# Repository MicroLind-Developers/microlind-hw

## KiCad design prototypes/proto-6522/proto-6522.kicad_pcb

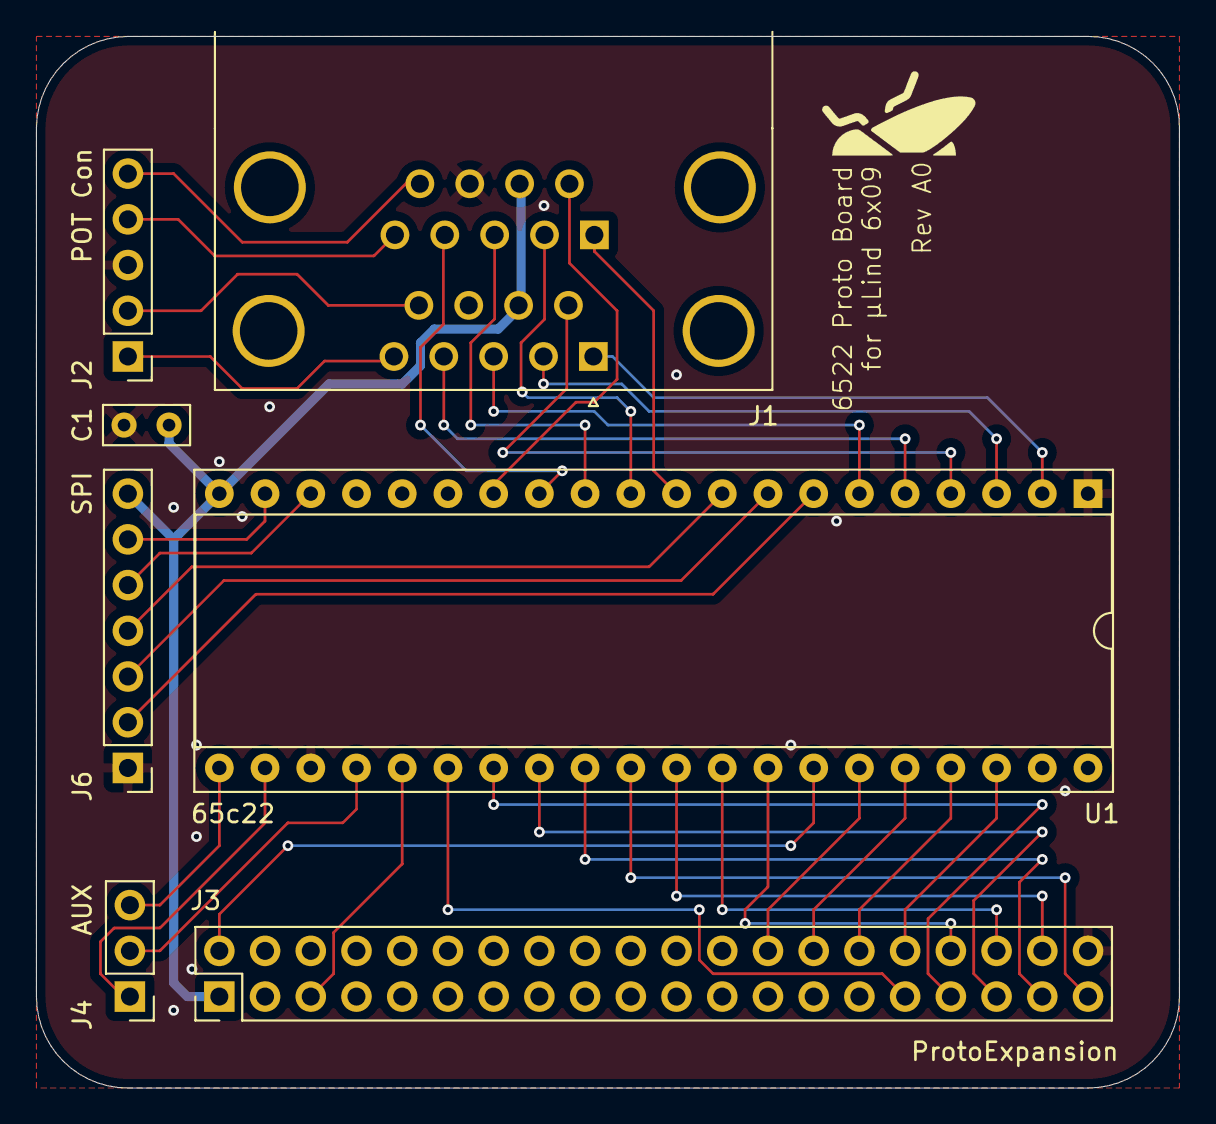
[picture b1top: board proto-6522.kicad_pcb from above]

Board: 2 copper layers, 63.5 x 58.4 mm, 7 parts (0 on the bottom side), 38 nets.

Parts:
C1: C; C_Rect_L4.6mm_W2.0mm_P2.50mm_MKS02_FKP02
J1: DSUB-9-Double_NorComp
J2: POT Con; PinHeader_1x05_P2.54mm_Vertical
J3: ProtoExpansion; PinHeader_2x20_P2.54mm_Vertical
J4: AUX; PinHeader_1x03_P2.54mm_Vertical
J6: SPI; PinHeader_1x07_P2.54mm_Vertical
U1: 65c22; DIP-40_W15.24mm_Socket

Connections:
/A0: J3.32, U1.38 (RS0)
/A1: J3.30, U1.37 (RS1)
/A2: J3.28, U1.36 (RS2)
/A3: J3.26, U1.35 (RS3)
/COPI/CIPO: J6.6, U1.19 (CB2)
/CS0: J6.2, U1.7 (PA5)
/CS1: J6.3, U1.8 (PA6)
/CS2: J6.4, U1.9 (PA7)
/D0: J3.34, U1.33 (D0)
/D1: J3.36, U1.32 (D1)
/D2: J3.38, U1.31 (D2)
/D3: J3.39, U1.30 (D3)
/D4: J3.37, U1.29 (D4)
/D5: J3.35, U1.28 (D5)
/D6: J3.33, U1.27 (D6)
/D7: J3.31, U1.26 (D7)
/E: J3.5, U1.25 (ϕ2)
/R/~W: J4.1, U1.22 (R/~W)
/SCK: J6.5, U1.18 (CB1)
/~INT_PAR: J4.3, U1.21 (~IRQ)
/~PAR_EN: J4.2, U1.24 (CS1)
/~RST: J3.2, U1.34 (~RES)
GND: C1.2, J1.8, J1.18, J2.3, J3.40, J6.1, U1.1 (VSS), U1.23 (~CS2)
unnamed: J1.5, J2.1
unnamed: J1.9, J2.2
unnamed: J1.15, J2.4
unnamed: J1.19, J2.5
unnamed: J1.1, U1.2 (PA0)
unnamed: J1.2, U1.3 (PA1)
unnamed: J1.6, U1.4 (PA2)
unnamed: J1.4, U1.5 (PA3)
unnamed: J1.3, U1.6 (PA4)
unnamed: J1.11, U1.10 (PB0)
unnamed: J1.12, U1.11 (PB1)
unnamed: J1.13, U1.12 (PB2)
unnamed: J1.14, U1.13 (PB3)
unnamed: J1.16, U1.14 (PB4)
VCC: C1.1, J1.7, J1.17, J3.1, J6.7, U1.20 (VCC)

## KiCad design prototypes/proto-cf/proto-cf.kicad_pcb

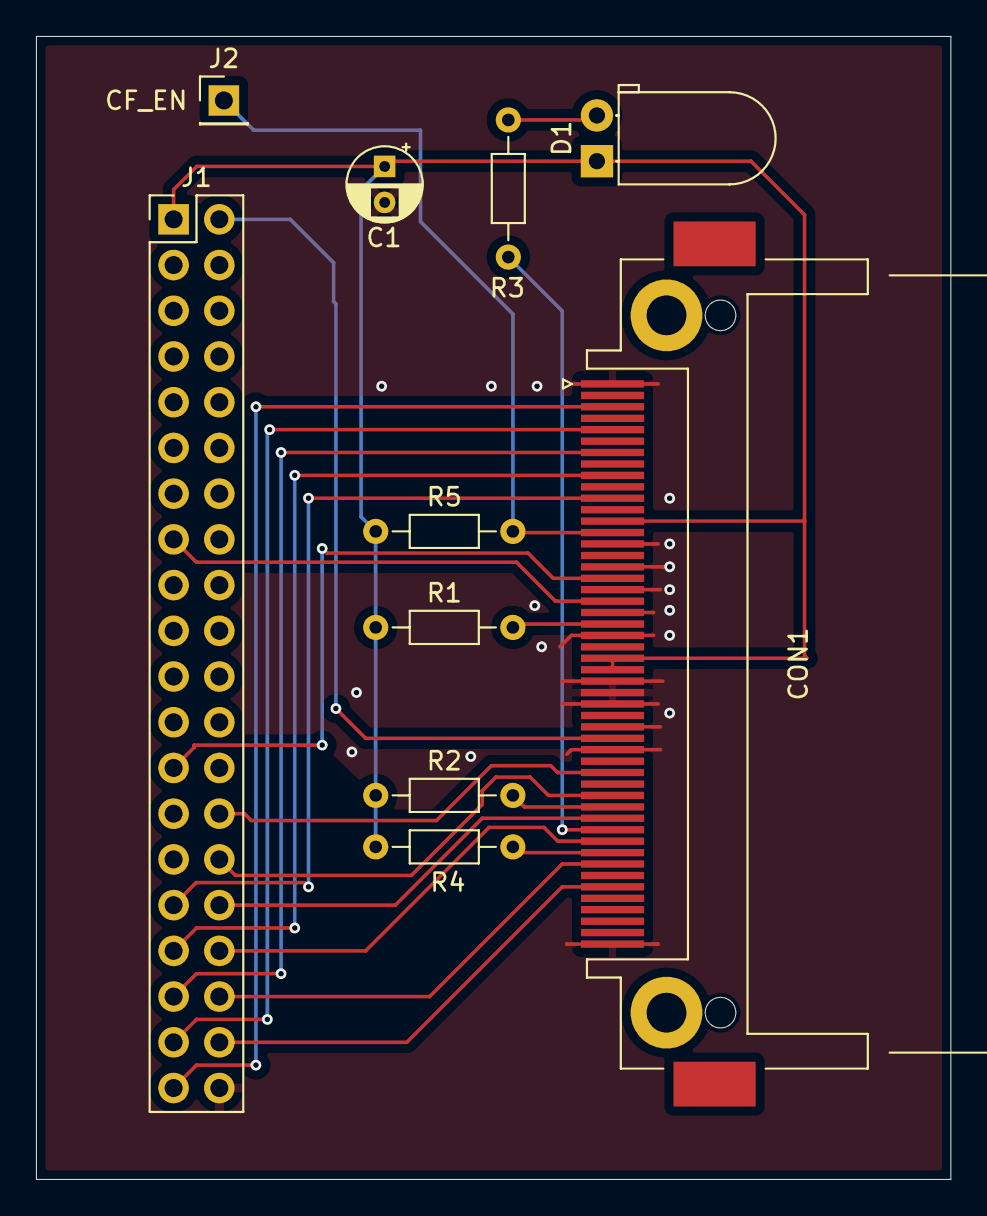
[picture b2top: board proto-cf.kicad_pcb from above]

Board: 2 copper layers, 50.8 x 63.5 mm, 10 parts (0 on the bottom side), 22 nets.

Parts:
C1: C_Polarized; CP_Radial_D4.0mm_P2.00mm
CON1: CF-CARD; CF-Card_3M_N7E50-7516PK-20-WF
D1: LED; LED_D5.0mm_Horizontal_O1.27mm_Z3.0mm_Clear
J1: VideoExpansion; PinHeader_2x20_P2.54mm_Vertical
J2: CF_EN; PinHeader_1x01_P2.54mm_Vertical
R1, R2, R3, R4, R5: 4k7; R_Axial_DIN0204_L3.6mm_D1.6mm_P7.62mm_Horizontal

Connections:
/A0: CON1.20 (A0), J1.32
/A1: CON1.19 (A1), J1.30
/A2: CON1.18 (A2), J1.28
/D0: CON1.21 (D0), J1.34
/D1: CON1.22 (D1), J1.36
/D2: CON1.23 (D2), J1.38
/D3: CON1.2 (D3), J1.39
/D4: CON1.3 (D4), J1.37
/D5: CON1.4 (D5), J1.35
/D6: CON1.5 (D6), J1.33
/D7: CON1.6 (D7), J1.31
/~CF_EN: CON1.32 (/CS1), J2.1, R5.2
/~RD: CON1.34 (/IORD), J1.25
/~RST: CON1.41 (/RESET), J1.2
/~WR: CON1.35 (/IOWR), J1.15
GND: C1.2, CON1.1 (GND1), CON1.8 (A10), CON1.9 (/ATASEL), CON1.10 (A9), CON1.11 (A8), CON1.12 (A7), CON1.14 (A6), CON1.15 (A5), CON1.16 (A4), CON1.17 (A3), CON1.39 (/CSEL), CON1.50 (GND2), J1.40
unnamed: CON1.45 (/DASP), R3.2
unnamed: CON1.46 (/PDIAG), R4.2
unnamed: CON1.44 (/REG), R2.2
unnamed: CON1.36 (/WE), R1.2
unnamed: D1.2 (A), R3.1
VCC: C1.1, CON1.7 (/CS0), CON1.13 (VCC2), CON1.38 (VCC1), D1.1 (K), J1.1, R1.1, R2.1, R4.1, R5.1

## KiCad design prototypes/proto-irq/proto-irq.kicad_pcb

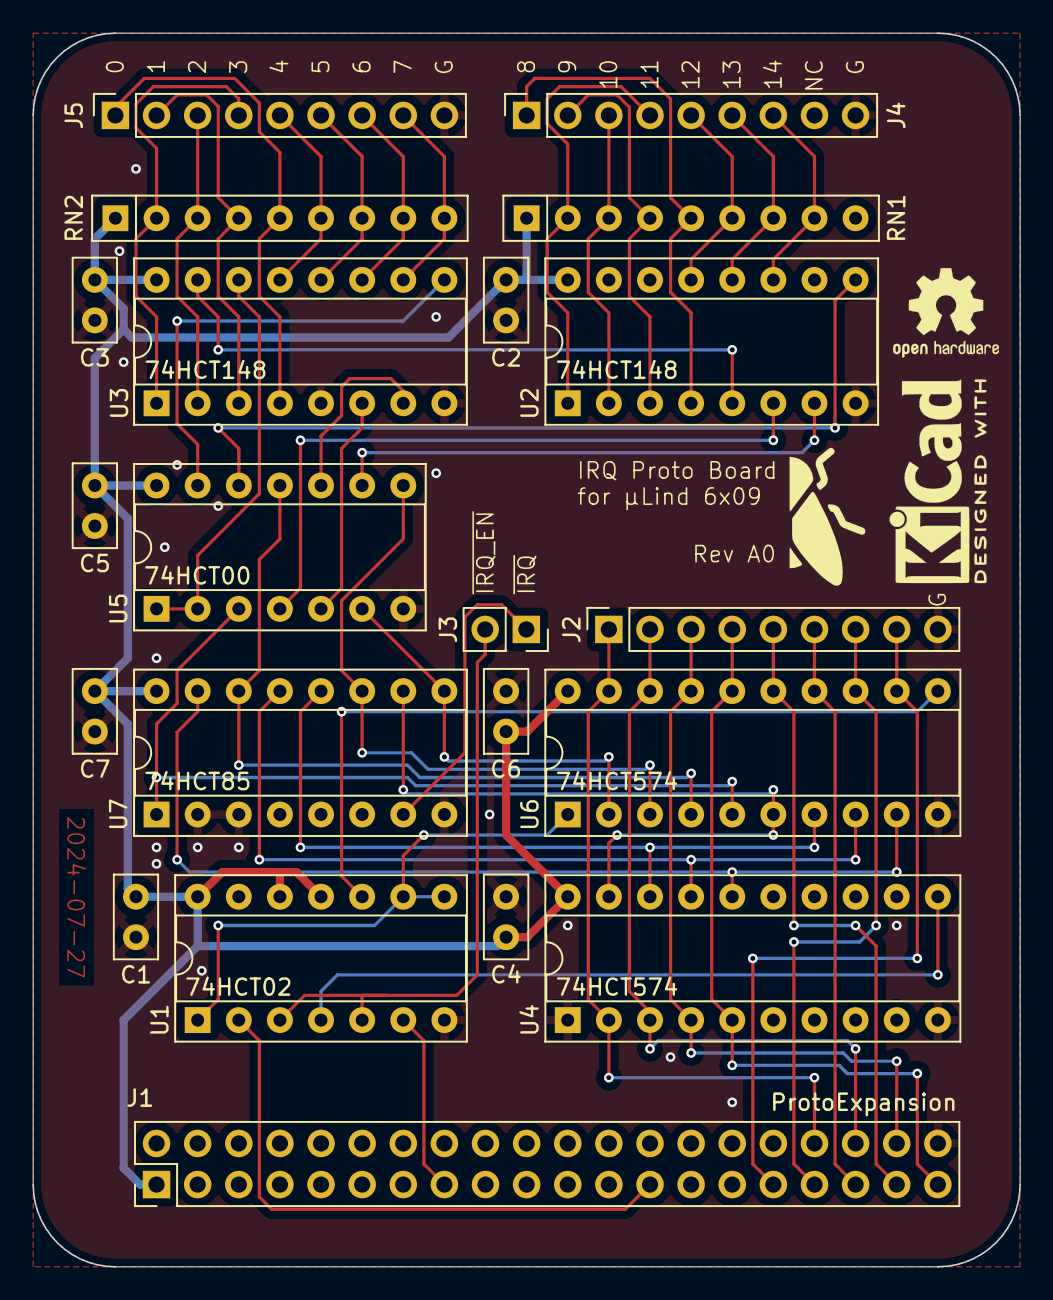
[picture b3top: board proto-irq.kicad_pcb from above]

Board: 2 copper layers, 61.0 x 76.2 mm, 21 parts (0 on the bottom side), 48 nets.

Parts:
C1, C2, C3, C4, C5, C6, C7: 100n; C_Disc_D5.0mm_W2.5mm_P2.50mm
J1: ProtoExpansion; PinHeader_2x20_P2.54mm_Vertical
J2: DataValue; PinSocket_1x09_P2.54mm_Vertical
J3: AUX; PinSocket_1x02_P2.54mm_Vertical
J4: Low IRQ; PinSocket_1x09_P2.54mm_Vertical
J5: High IRQ; PinSocket_1x09_P2.54mm_Vertical
RN1, RN2: R_Network08; R_Array_SIP9
U1: 74HCT02; DIP-14_W7.62mm_Socket
U2, U3: 74HCT148; DIP-16_W7.62mm_Socket
U4, U6: 74HCT574; DIP-20_W7.62mm_Socket
U5: 74HCT00; DIP-14_W7.62mm_Socket
U7: 74HCT85; DIP-16_W7.62mm_Socket

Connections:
/D0: J1.34, J2.1, U4.2 (D0), U6.19 (Q0)
/D1: J1.36, J2.2, U4.3 (D1), U6.18 (Q1)
/D2: J1.38, J2.3, U4.4 (D2), U6.17 (Q2)
/D3: J1.39, J2.4, U4.5 (D3), U6.16 (Q3)
/D4: J1.37, J2.5, U6.15 (Q4)
/D5: J1.35, J2.6, U6.14 (Q5)
/D6: J1.33, J2.7, U6.13 (Q6)
/D7: J1.31, J2.8, U6.12 (Q7)
/~IRQ_EN: J3.2, U1.3, U1.5
/~IRQ: J3.1, U7.7 (Oa<b)
/~RD: J1.25, U1.2
/~WR: J1.15, U1.6
GND: C1.2, C2.2, C3.2, C4.2, C5.2, C6.2, C7.2, J1.40, J2.9, J4.9, J5.9, U1.7 (GND), U2.8 (GND), U3.5 (EI), U3.8 (GND), U4.1 (OE), U4.10 (GND), U5.7 (GND), U6.10 (GND), U7.2 (Ia<b), U7.3 (Ia=b), U7.4 (Ia>b), U7.8 (GND)
unnamed: U2.5 (EI), U3.15 (EO)
unnamed: U2.9 (S0), U5.12
unnamed: U2.7 (S1), U5.9
unnamed: U2.6 (S2), U5.4
unnamed: U3.14 (GS), U5.1, U5.2
unnamed: U3.9 (S0), U5.13
unnamed: U3.7 (S1), U5.10
unnamed: U3.6 (S2), U5.5
unnamed: U1.4, U4.11 (Cp)
unnamed: U4.19 (Q0), U6.6 (D4), U7.10 (A0)
unnamed: U4.18 (Q1), U6.7 (D5), U7.12 (A1)
unnamed: U4.17 (Q2), U6.8 (D6), U7.13 (A2)
unnamed: U4.16 (Q3), U6.9 (D7), U7.15 (A3)
unnamed: U1.10, U6.11 (Cp)
unnamed: U5.6, U6.2 (D0), U7.9 (B0)
unnamed: U5.8, U6.3 (D1), U7.11 (B1)
unnamed: U5.11, U6.4 (D2), U7.14 (B2)
unnamed: U5.3, U6.5 (D3), U7.1 (B3)
unnamed: U1.1, U1.8, U1.9, U6.1 (OE)
VCC: C1.1, C2.1, C3.1, C4.1, C5.1, C6.1, C7.1, J1.1, RN1.1 (common), RN2.1 (common), U1.11, U1.12, U1.14 (VCC), U2.16 (VCC), U3.16 (VCC), U4.20 (VCC), U5.14 (VCC), U6.20 (VCC), U7.16 (VCC)
~IRQ_0: J5.1, RN2.5 (R4), U3.4 (I7)
~IRQ_1: J5.2, RN2.4 (R3), U3.3 (I6)
~IRQ_2: J5.3, RN2.3 (R2), U3.2 (I5)
~IRQ_3: J5.4, RN2.2 (R1), U3.1 (I4)
~IRQ_4: J5.5, RN2.6 (R5), U3.13 (I3)
~IRQ_5: J5.6, RN2.7 (R6), U3.12 (I2)
~IRQ_6: J5.7, RN2.8 (R7), U3.11 (I1)
~IRQ_7: J5.8, RN2.9 (R8), U3.10 (IO)
~IRQ_8: J4.1, RN1.5 (R4), U2.4 (I7)
~IRQ_9: J4.2, RN1.4 (R3), U2.3 (I6)
~IRQ_10: J4.3, RN1.3 (R2), U2.2 (I5)
~IRQ_11: J4.4, RN1.2 (R1), U2.1 (I4)
~IRQ_12: J4.5, RN1.6 (R5), U2.13 (I3)
~IRQ_13: J4.6, RN1.7 (R6), U2.12 (I2)
~IRQ_14: J4.7, RN1.8 (R7), U2.11 (I1)

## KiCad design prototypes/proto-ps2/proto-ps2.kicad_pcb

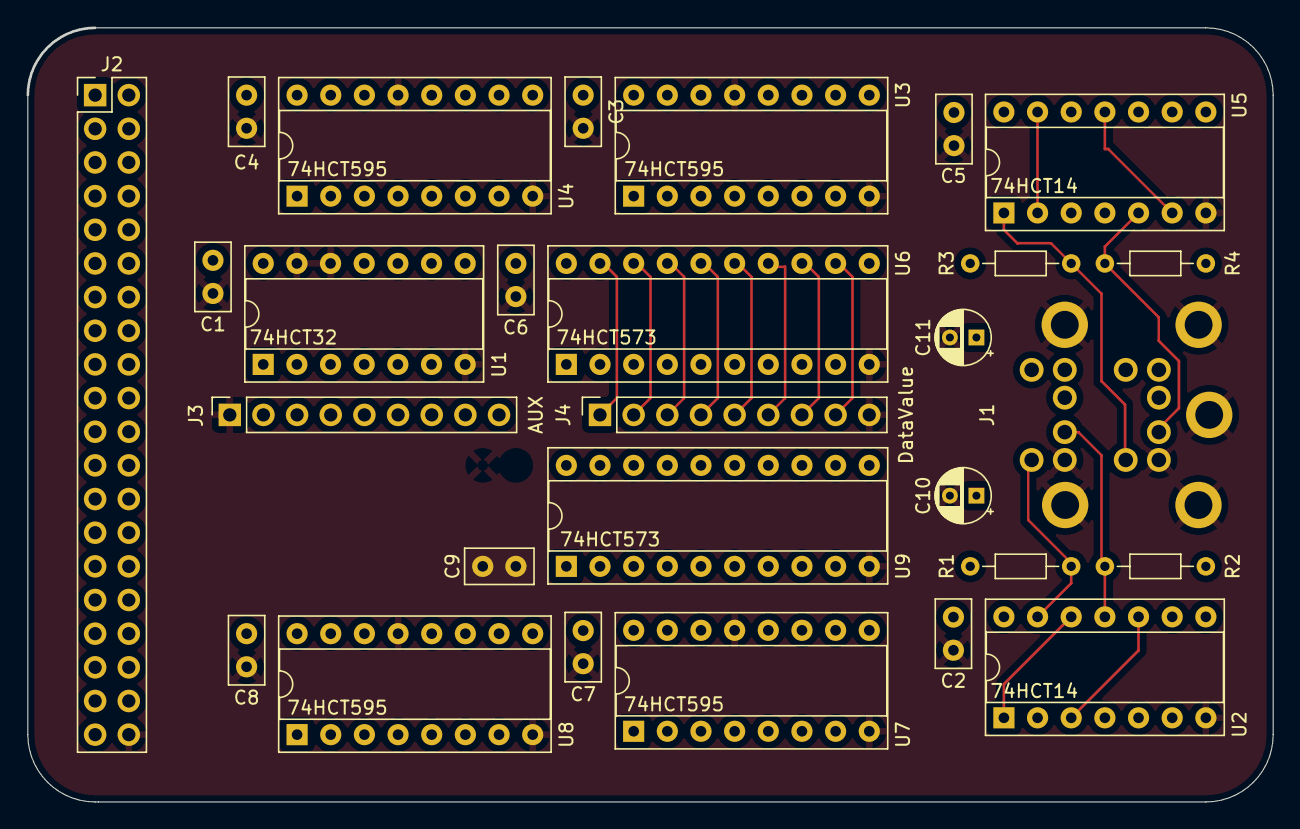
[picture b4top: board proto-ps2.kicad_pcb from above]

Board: 2 copper layers, 94.0 x 58.4 mm, 28 parts (0 on the bottom side), 53 nets.

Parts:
C1, C2, C3, C4, C5, C6, C7, C8, C9: 100n; C_Disc_D5.0mm_W2.5mm_P2.50mm
C10, C11: 10u; CP_Radial_D4.0mm_P2.00mm
J1: 2xPS2-Mini-Din
J2: VideoExpansion; PinHeader_2x20_P2.54mm_Vertical
J3: AUX; PinSocket_1x09_P2.54mm_Vertical
J4: DataValue; PinSocket_1x09_P2.54mm_Vertical
R1, R2, R3, R4: 10k; R_Axial_DIN0204_L3.6mm_D1.6mm_P7.62mm_Horizontal
U1: 74HCT32; DIP-14_W7.62mm_Socket
U2, U5: 74HCT14; DIP-14_W7.62mm_Socket
U3, U4, U7, U8: 74HCT595; DIP-16_W7.62mm_Socket
U6, U9: 74HCT573; DIP-20_W7.62mm_Socket

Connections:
/D0: J2.34, J4.1, U6.19 (Q0), U9.19 (Q0)
/D1: J2.36, J4.2, U6.18 (Q1), U9.18 (Q1)
/D2: J2.38, J4.3, U6.17 (Q2), U9.17 (Q2)
/D3: J2.39, J4.4, U6.16 (Q3), U9.16 (Q3)
/D4: J2.37, J4.5, U6.15 (Q4), U9.15 (Q4)
/D5: J2.35, J4.6, U6.14 (Q5), U9.14 (Q5)
/D6: J2.33, J4.7, U6.13 (Q6), U9.13 (Q6)
/D7: J2.31, J4.8, U6.12 (Q7), U9.12 (Q7)
/E: J2.5, J3.5, U3.12 (RCLK), U4.12 (RCLK), U7.12 (RCLK), U8.12 (RCLK)
/M_CLK: U2.2, U3.11 (SRCLK), U4.11 (SRCLK)
/M_DATA: U2.4, U3.14 (SER)
/PS2_KB_CLK: J1.11 (Kbd_Clock), R3.2, U5.1
/PS2_KB_DATA: J1.7 (Kbd_Data), R4.2, U5.5
/PS2_M_CLK: J1.5 (Mouse_Clock), R1.2, U2.13
/PS2_M_DATA: J1.1 (Mouse_Data), R2.2, U2.11
/~INT_PS2_KB: J3.4, U5.8
/~INT_PS2_M: J3.2, U2.8
/~PS2_EN: J3.3, U1.2
/~RD: J2.25, J3.6, U1.1
/~RST: J2.2, J3.7, U3.10 (~SRCLR), U4.10 (~SRCLR), U7.10 (~SRCLR), U8.10 (~SRCLR)
A0: J2.32, J3.8, U1.4, U5.3
GND: C1.2, C2.2, C3.2, C4.2, C5.2, C6.2, C7.2, C8.2, C9.2, C10.2, C11.2, J1.3 (Mouse_GND), J1.9 (Kbd_GND), J1.G (GND), J2.40, J3.1, J4.9, U1.7 (GND), U1.12, U1.13, U2.7 (GND), U3.8 (GND), U3.13 (~OE), U4.8 (GND), U4.13 (~OE), U5.7 (GND), U6.10 (GND), U7.8 (GND), U7.13 (~OE), U8.8 (GND), U8.13 (~OE), U9.10 (GND)
unnamed: U1.3, U1.5, U1.9
unnamed: U1.10, U5.4
unnamed: U2.1, U2.12
unnamed: U2.3, U2.10
unnamed: U3.2 (QC), U6.9 (D7)
unnamed: U3.3 (QD), U6.8 (D6)
unnamed: U3.4 (QE), U6.7 (D5)
unnamed: U3.5 (QF), U6.6 (D4)
unnamed: U3.6 (QG), U6.5 (D3)
unnamed: U3.9 (QH'), U4.14 (SER)
unnamed: U3.7 (QH), U6.4 (D2)
unnamed: U4.15 (QA), U6.3 (D1)
unnamed: U4.1 (QB), U6.2 (D0)
unnamed: U2.9, U4.2 (QC), U6.11 (Load)
unnamed: U5.6, U5.11
unnamed: U5.2, U5.13
unnamed: U1.8, U6.1 (OE)
unnamed: U7.2 (QC), U9.9 (D7)
unnamed: U7.3 (QD), U9.8 (D6)
unnamed: U7.4 (QE), U9.7 (D5)
unnamed: U7.5 (QF), U9.6 (D4)
unnamed: U7.6 (QG), U9.5 (D3)
unnamed: U7.9 (QH'), U8.14 (SER)
unnamed: U7.7 (QH), U9.4 (D2)
unnamed: U5.10, U7.14 (SER)
unnamed: U5.12, U7.11 (SRCLK), U8.11 (SRCLK)
unnamed: U8.15 (QA), U9.3 (D1)
unnamed: U8.1 (QB), U9.2 (D0)
unnamed: U5.9, U8.2 (QC), U9.11 (Load)
unnamed: U1.6, U9.1 (OE)
VCC: C1.1, C2.1, C3.1, C4.1, C5.1, C6.1, C7.1, C8.1, C9.1, C10.1, C11.1, J1.4 (Mouse_PWR), J1.10 (Kbd_PWR), J2.1, J3.9, R1.1, R2.1, R3.1, R4.1, U1.14 (VCC), U2.5, U2.14 (VCC), U3.16 (VCC), U4.16 (VCC), U5.14 (VCC), U6.20 (VCC), U7.16 (VCC), U8.16 (VCC), U9.20 (VCC)
